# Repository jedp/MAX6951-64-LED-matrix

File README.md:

MAX6951 64-LED Matrix
---------------------

A breakout board of 64 "charlieplexed" LEDs. For use with the MAX6951.

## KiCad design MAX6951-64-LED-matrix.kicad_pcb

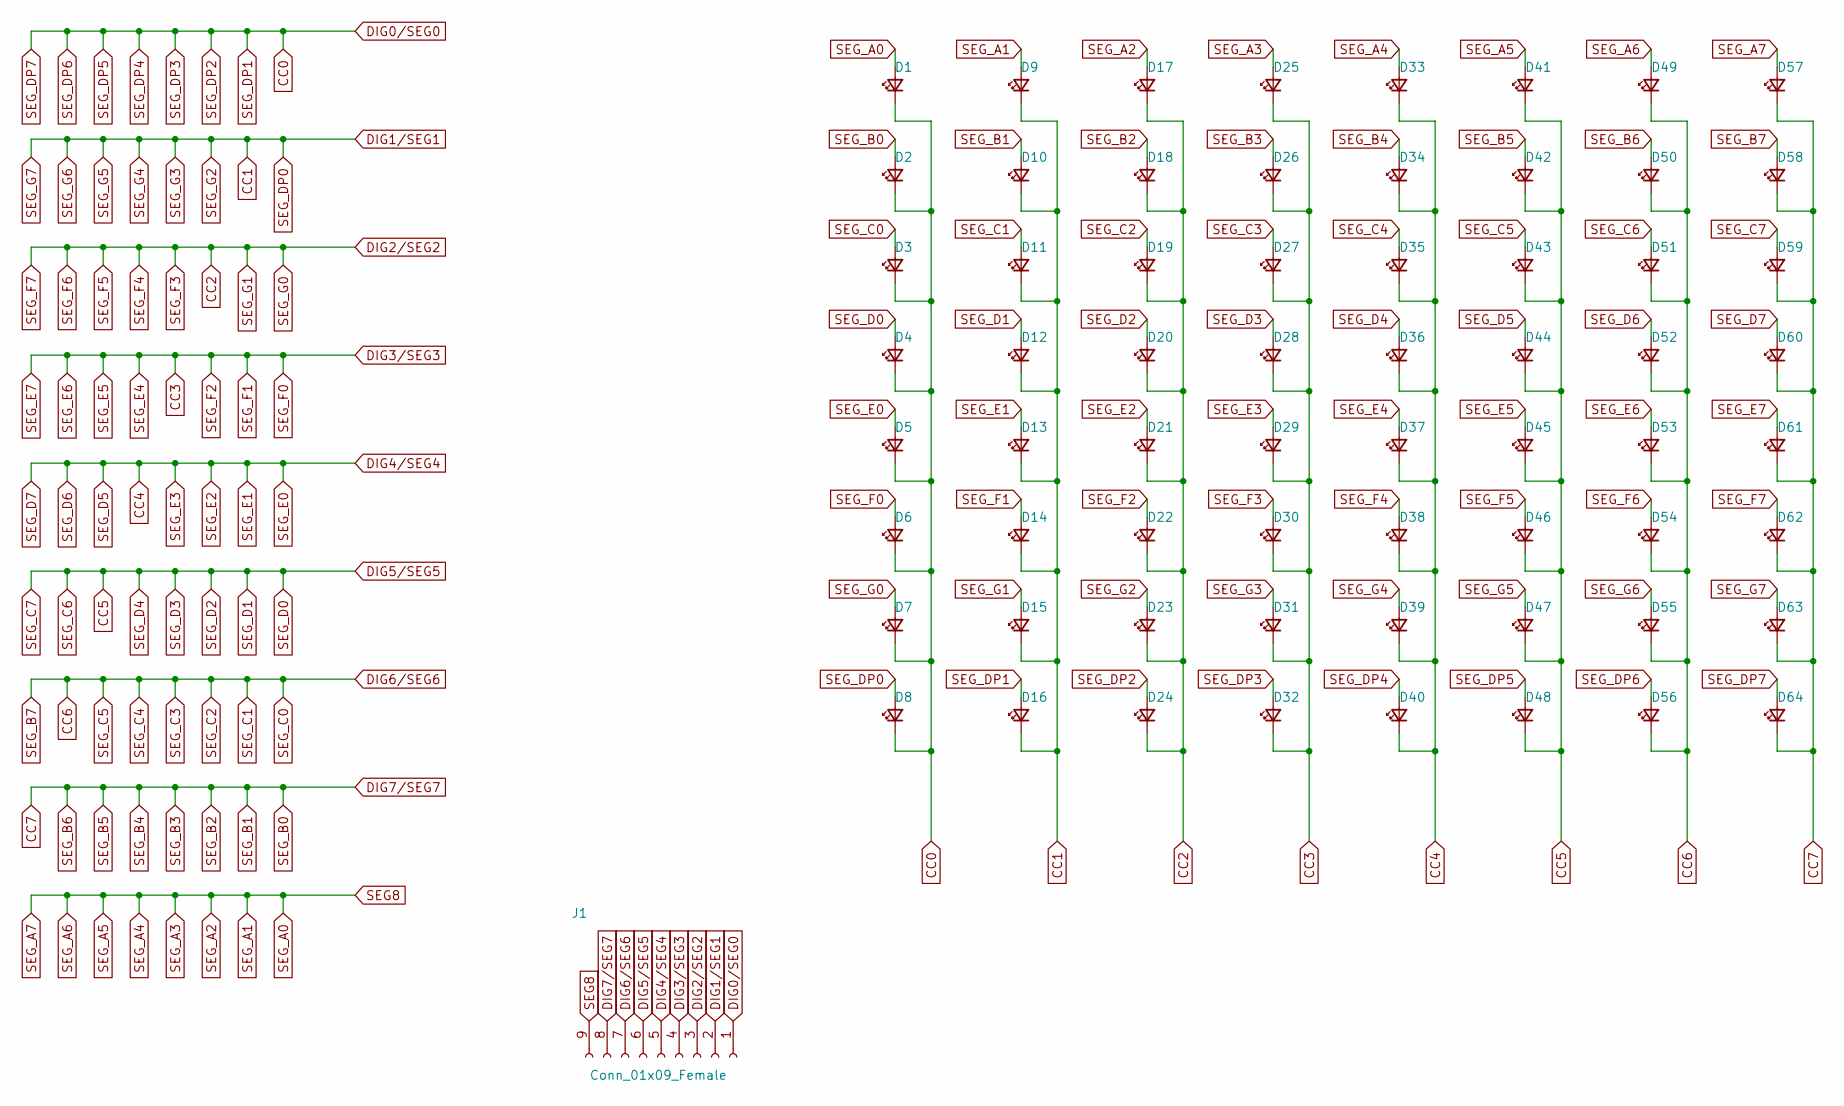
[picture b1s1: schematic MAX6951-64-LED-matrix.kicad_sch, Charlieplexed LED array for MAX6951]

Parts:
D1, D2, D3, D4, D5, D6, D7, D8, D9, D10, D11, D12, D13, D14, D15, D16, D17, D18, D19, D20, D21, D22, D23, D24, D25, D26, D27, D28, D29, D30, D31, D32, D33, D34, D35, D36, D37, D38, D39, D40, D41, D42, D43, D44, D45, D46, D47, D48, D49, D50, D51, D52, D53, D54, D55, D56, D57, D58, D59, D60, D61, D62, D63, D64: LED_Small; LED_0603_1608Metric
J1: Conn_01x09_Female; PinHeader_1x09_P2.54mm_Vertical

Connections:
CC0: D1.1 (K), D2.1 (K), D3.1 (K), D4.1 (K), D5.1 (K), D6.1 (K), D7.1 (K), D8.1 (K), D16.2 (A), D24.2 (A), D32.2 (A), D40.2 (A), D48.2 (A), D56.2 (A), D64.2 (A), J1.1
CC1: D8.2 (A), D9.1 (K), D10.1 (K), D11.1 (K), D12.1 (K), D13.1 (K), D14.1 (K), D15.1 (K), D16.1 (K), D23.2 (A), D31.2 (A), D39.2 (A), D47.2 (A), D55.2 (A), D63.2 (A), J1.2
CC2: D7.2 (A), D15.2 (A), D17.1 (K), D18.1 (K), D19.1 (K), D20.1 (K), D21.1 (K), D22.1 (K), D23.1 (K), D24.1 (K), D30.2 (A), D38.2 (A), D46.2 (A), D54.2 (A), D62.2 (A), J1.3
CC3: D6.2 (A), D14.2 (A), D22.2 (A), D25.1 (K), D26.1 (K), D27.1 (K), D28.1 (K), D29.1 (K), D30.1 (K), D31.1 (K), D32.1 (K), D37.2 (A), D45.2 (A), D53.2 (A), D61.2 (A), J1.4
CC4: D5.2 (A), D13.2 (A), D21.2 (A), D29.2 (A), D33.1 (K), D34.1 (K), D35.1 (K), D36.1 (K), D37.1 (K), D38.1 (K), D39.1 (K), D40.1 (K), D44.2 (A), D52.2 (A), D60.2 (A), J1.5
CC5: D4.2 (A), D12.2 (A), D20.2 (A), D28.2 (A), D36.2 (A), D41.1 (K), D42.1 (K), D43.1 (K), D44.1 (K), D45.1 (K), D46.1 (K), D47.1 (K), D48.1 (K), D51.2 (A), D59.2 (A), J1.6
CC6: D3.2 (A), D11.2 (A), D19.2 (A), D27.2 (A), D35.2 (A), D43.2 (A), D49.1 (K), D50.1 (K), D51.1 (K), D52.1 (K), D53.1 (K), D54.1 (K), D55.1 (K), D56.1 (K), D58.2 (A), J1.7
CC7: D2.2 (A), D10.2 (A), D18.2 (A), D26.2 (A), D34.2 (A), D42.2 (A), D50.2 (A), D57.1 (K), D58.1 (K), D59.1 (K), D60.1 (K), D61.1 (K), D62.1 (K), D63.1 (K), D64.1 (K), J1.8
SEG8: D1.2 (A), D9.2 (A), D17.2 (A), D25.2 (A), D33.2 (A), D41.2 (A), D49.2 (A), D57.2 (A), J1.9

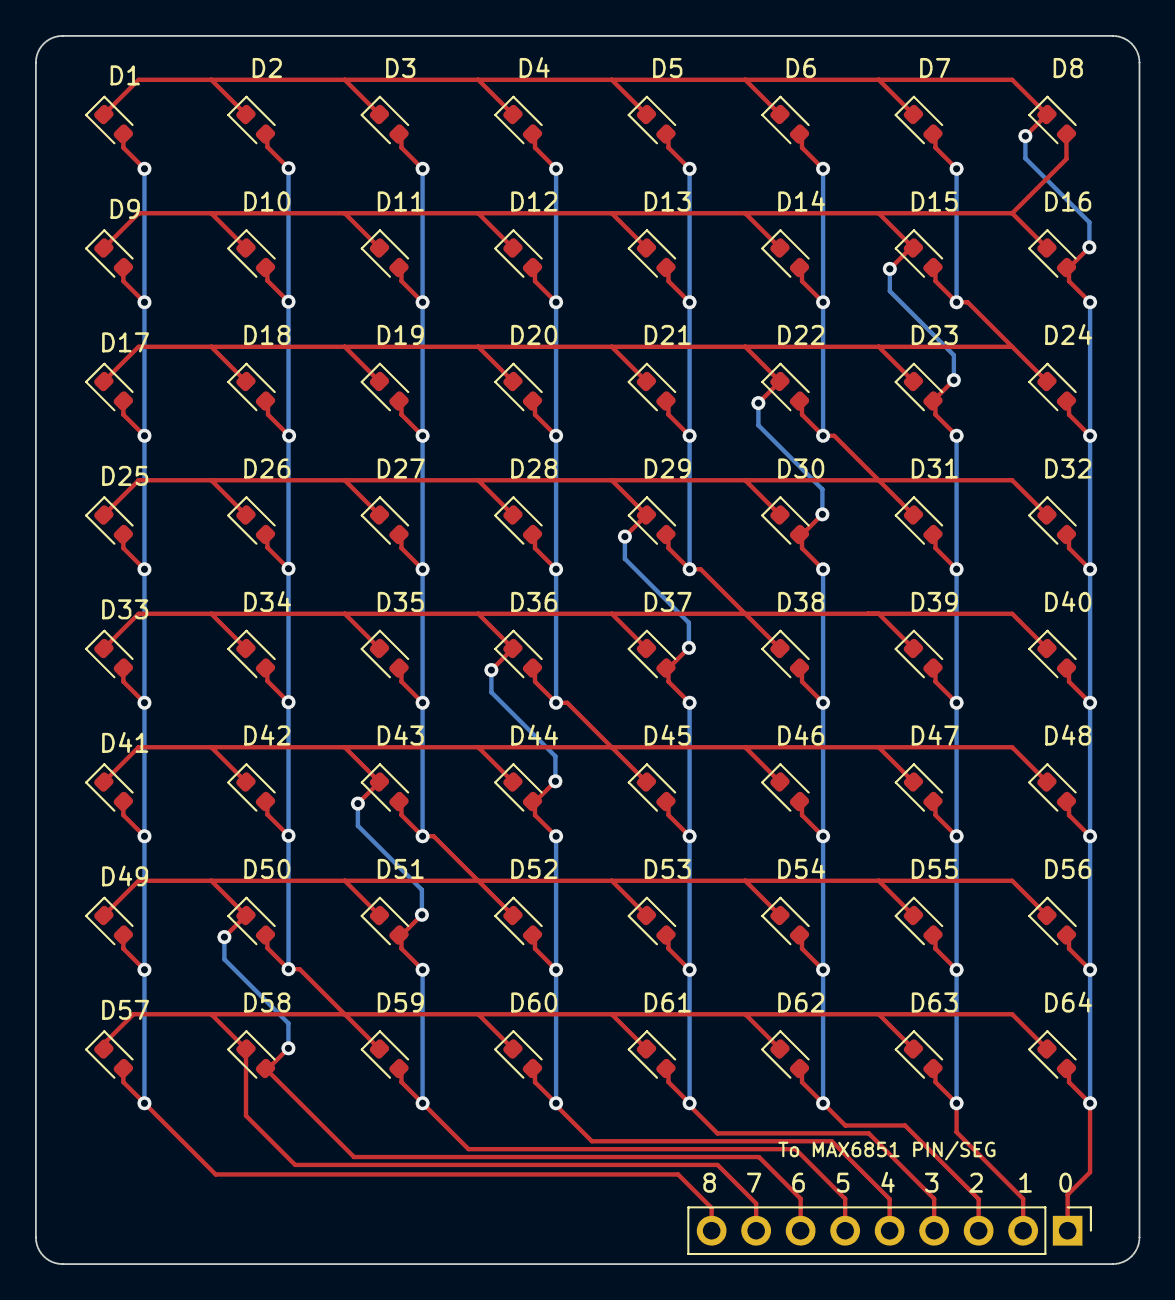
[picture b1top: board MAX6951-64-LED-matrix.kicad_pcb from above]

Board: 2 copper layers, 63.0 x 70.1 mm, 65 parts (0 on the bottom side), 9 nets.

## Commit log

2023-01-16 MAX6951 64-LED matrix
2023-01-16 Added image
